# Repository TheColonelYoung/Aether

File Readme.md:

# AETHER
Addressable LED controller powered by WLED. Sound reactive capable with IR receiver. Due to ESP32 is capable to produce FFT effects.
Designed as replacement electronics for SP511e. So it fits the same case.

### Features and components
- Compatible with 12V and 5V strips
- Built-on digital microphone (INMP411) 
    - Works with Sound reactive fork
    - Support FFT effects
- IR receiver for remote control
- Bootloader jumper
- 3 buttons for manual control

### SP511e replacement
This project is designed as replacement for SP511e electronics which is based on ESP8266 which is not capable of FFT effect and can only driver one line of LED strips.
You don't need to have SP511e controller but some part are salvageable. You can 3D print your own case.
Microphone is also replaced with digital omni-directional which has better results.

Some parts are salvageable from original board:
- Cables for LEDs
- IR receiver with cable
- Buttons
- Input power jack
- Case

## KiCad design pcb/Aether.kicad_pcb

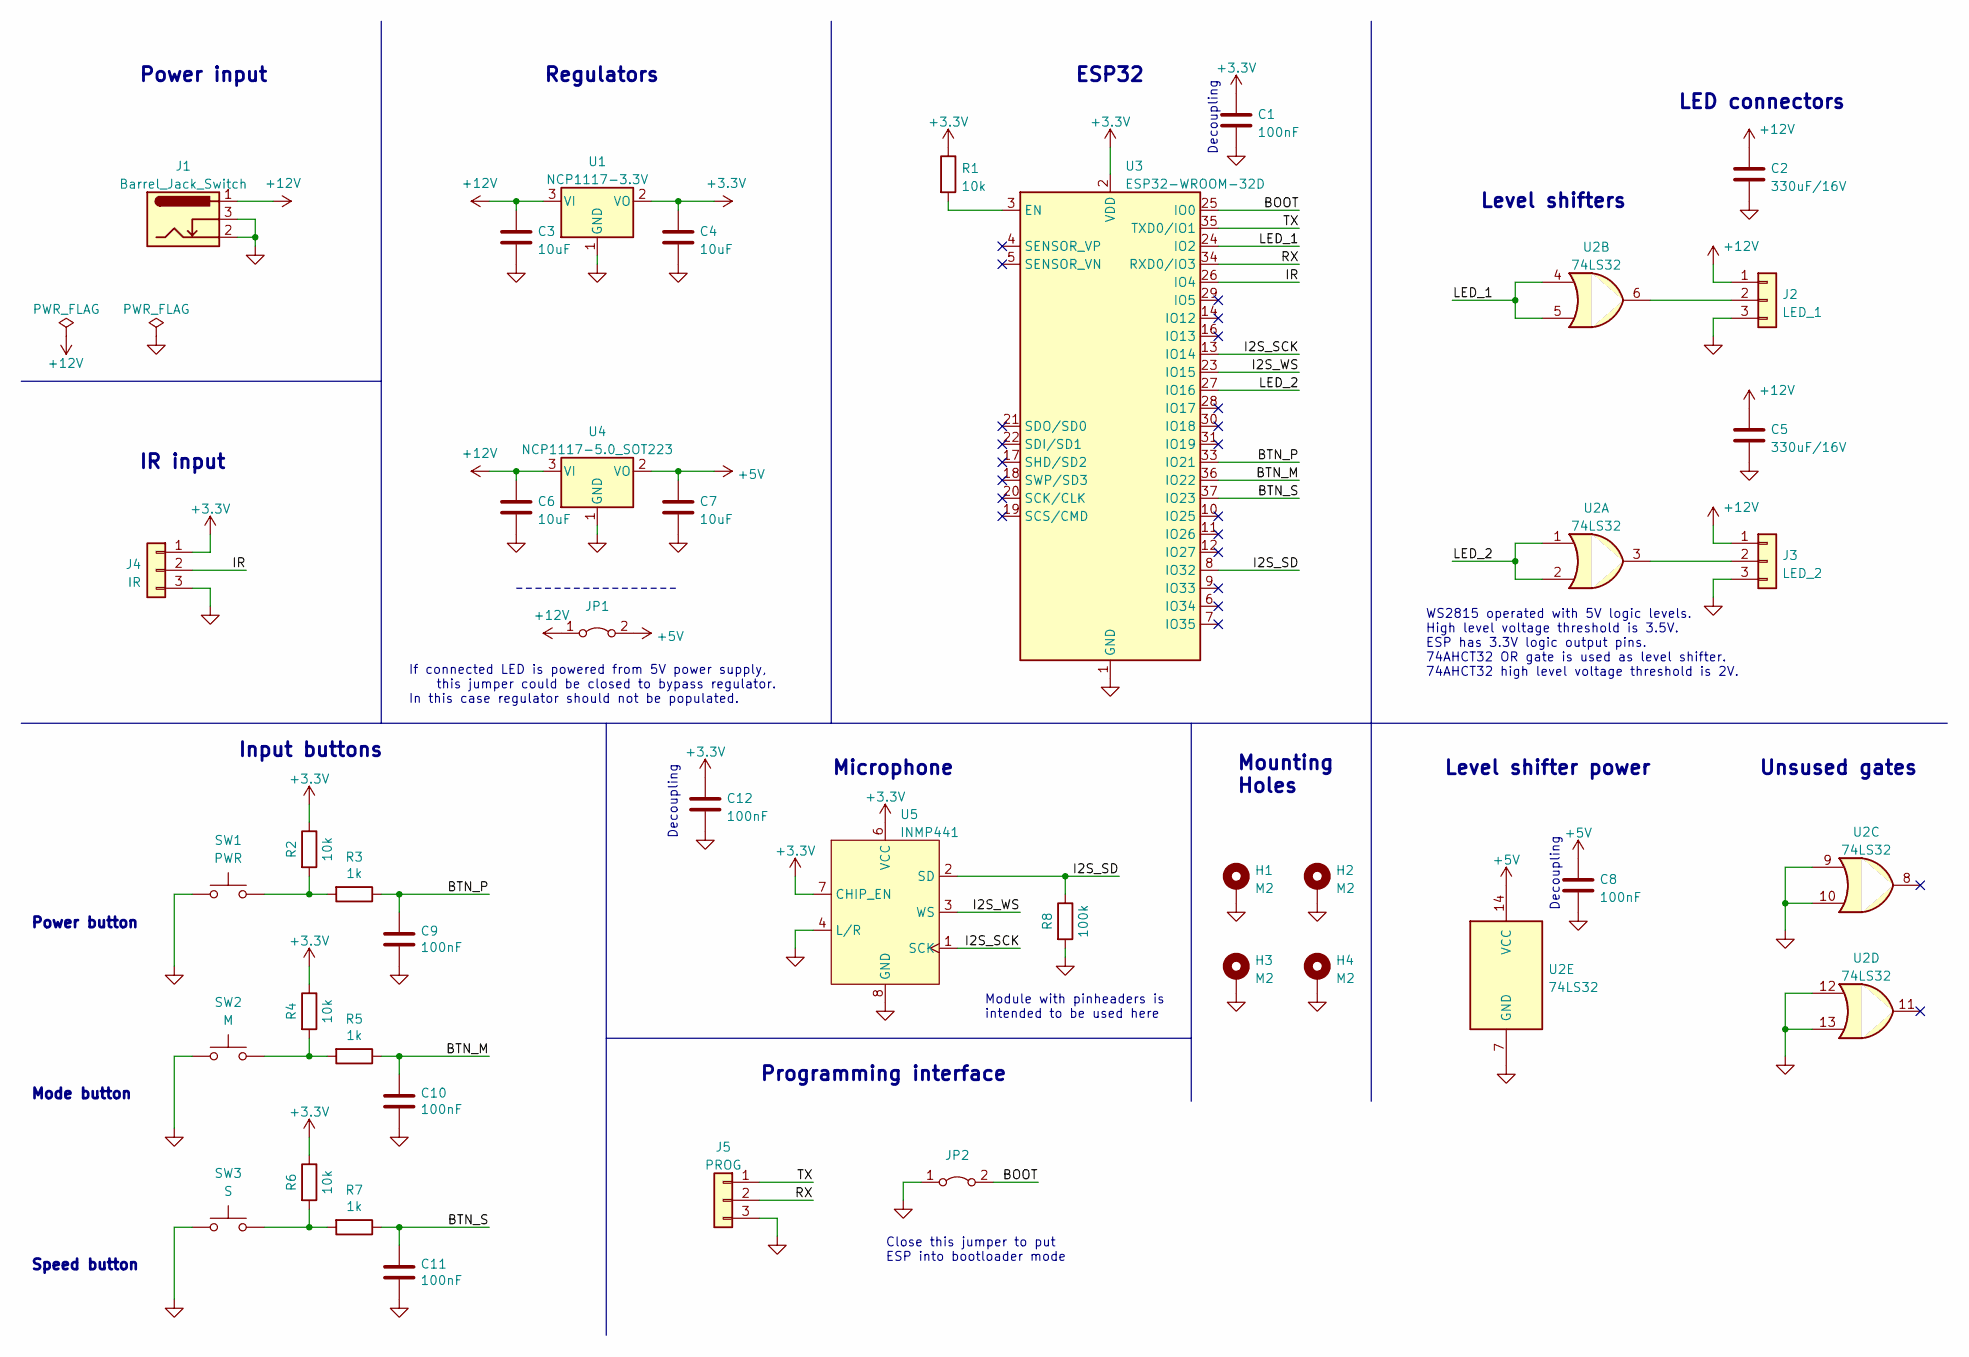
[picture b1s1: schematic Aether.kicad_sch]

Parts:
C1, C8, C9, C10, C11, C12: 100nF; C_0603_1608Metric
C2, C5: 330uF/16V; CP_Elec_6.3x7.7
C3, C4, C6, C7: 10uF; C_0805_2012Metric
H1, H2, H3, H4: M2; MountingHole_2.2mm_M2_Pad_Via
J1: Barrel_Jack_Switch; Barrel_jack_short
J2: LED_1; PinHeader_1x03_P2.54mm_Vertical
J3: LED_2; PinHeader_1x03_P2.54mm_Vertical
J4: IR; PinHeader_1x03_P2.54mm_Vertical
J5: PROG; PinHeader_1x03_P2.54mm_Vertical
JP1: 5V_PASSTHROUGH; SolderJumper-2_P1.3mm_Open_RoundedPad1.0x1.5mm
JP2: BOOT; PinHeader_1x02_P2.54mm_Vertical
R1, R2, R4, R6: 10k; R_0603_1608Metric
R3, R5, R7: 1k; R_0603_1608Metric
R8: 100k; R_0603_1608Metric
SW1: PWR; SW_SPST_TL3342
SW2: M; SW_SPST_TL3342
SW3: S; SW_SPST_TL3342
U1: NCP1117-3.3V; SOT-223-3_TabPin2
U2: 74LS32; Texas_S-PVQFN-N14
U3: ESP32-WROOM-32D; ESP32-WROOM-32
U4: NCP1117-5.0_SOT223; SOT-223-3_TabPin2
U5: INMP441

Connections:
+3.3V: C1.1, C4.1, C12.1, J4.1, R1.1, R2.1, R4.1, R6.1, U1.2 (VO), U3.2 (VDD), U5.6 (VCC), U5.7 (CHIP_EN)
+5V: C7.1, C8.1, JP1.2 (B), U2.14 (VCC), U4.2 (VO)
+12V: C2.1, C3.1, C5.1, C6.1, J1.1, J2.1, J3.1, JP1.1 (A), U1.3 (VI), U4.3 (VI)
/BOOT: JP2.2 (B), U3.25 (IO0)
/BTN_M: C10.1, R5.1, U3.36 (IO22)
/BTN_P: C9.1, R3.1, U3.33 (IO21)
/BTN_S: C11.1, R7.1, U3.37 (IO23)
/I2S_SCK: U3.13 (IO14), U5.1 (SCK)
/I2S_SD: R8.1, U3.8 (IO32), U5.2 (SD)
/I2S_WS: U3.23 (IO15), U5.3 (WS)
/IR: J4.2, U3.26 (IO4)
/LED_1: U2.4, U2.5, U3.24 (IO2)
/LED_2: U2.1, U2.2, U3.27 (IO16)
/RX: J5.2, U3.34 (RXD0/IO3)
/TX: J5.1, U3.35 (TXD0/IO1)
GND: C1.2, C2.2, C3.2, C4.2, C5.2, C6.2, C7.2, C8.2, C9.2, C10.2, C11.2, C12.2, H1.1, H2.1, H3.1, H4.1, J1.2, J1.3, J2.3, J3.3, J4.3, J5.3, JP2.1 (A), R8.2, SW1.1, SW2.1, SW3.1, U1.1 (GND), U2.7 (GND), U2.9, U2.10, U2.12, U2.13, U3.1 (GND), U3.15 (GND), U3.38 (GND), U3.39 (GND), U4.1 (GND), U5.4 (L/R), U5.5 (GND), U5.8 (GND), U5.9 (GND)
unnamed: J2.2, U2.6
unnamed: J3.2, U2.3
unnamed: R1.2, U3.3 (EN)
unnamed: R2.2, R3.2, SW1.2
unnamed: R4.2, R5.2, SW2.2
unnamed: R6.2, R7.2, SW3.2

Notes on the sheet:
Regulators
IR input
WS2815 operated with 5V logic levels. High level voltage threshold is 3.5V. ESP has 3.3V logic output pins. 74AHCT32 OR gate is used as level shifter. 74AHCT32 high level voltage threshold is 2V.
Decoupling
Level shifter power
Input buttons
Power button
Level shifters
Programming interface
LED connectors
ESP32
Mounting Holes
Power input
Close this jumper to put ESP into bootloader mode
Microphone
If connected LED is powered from 5V power supply, this jumper could be closed to bypass regulator. In this case regulator should not be populated.
Module with pinheaders is intended to be used here
Unsused gates
Speed button
Mode button

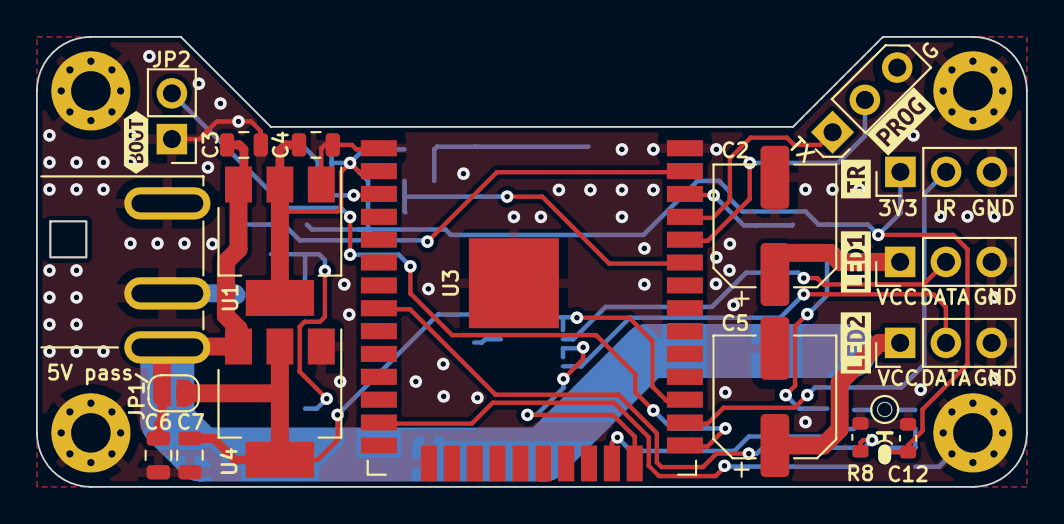
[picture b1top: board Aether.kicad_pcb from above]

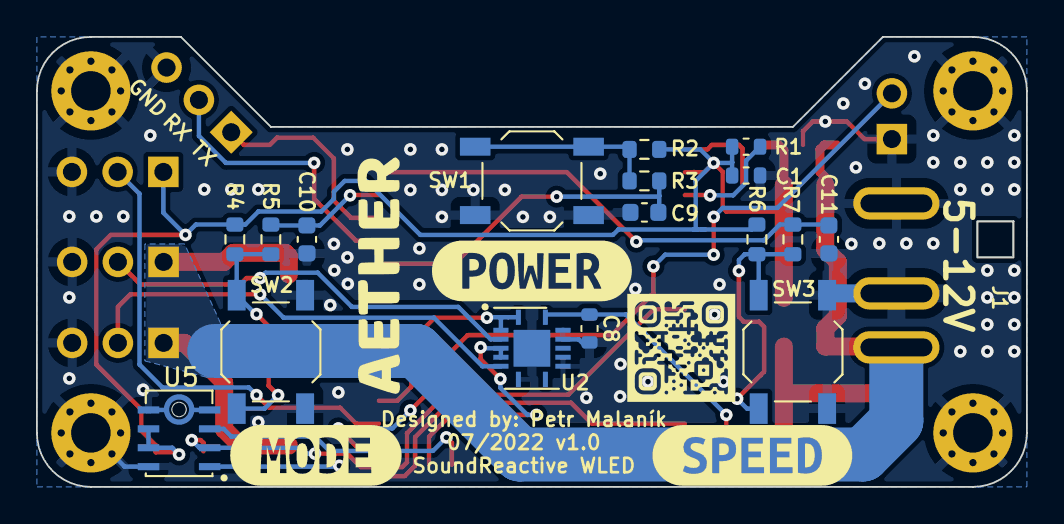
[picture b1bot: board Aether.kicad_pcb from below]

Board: 2 copper layers, 55.0 x 25.0 mm, 47 parts (20 on the bottom side), 22 nets.

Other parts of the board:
kibuzzard-62D1B70F: G***; kibuzzard-62D1B70F
kibuzzard-62D1B640: G***; kibuzzard-62D1B640
kibuzzard-62D1B654: G***; kibuzzard-62D1B654
kibuzzard-62D1B701: G***; kibuzzard-62D1B701
kibuzzard-62D2D12D: G***; kibuzzard-62D2D12D
kibuzzard-62D13E5B: G***; kibuzzard-62D13E5B
kibuzzard-62D13E43: G***; kibuzzard-62D13E43
kibuzzard-62D13E62: G***; kibuzzard-62D13E62

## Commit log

2022-07-11 Schema: Initial parts selection
2022-07-14 Schema: add level shifter, microphone and second LED output
2022-07-16 Schema: add microphone, mounting holes and finalize buttons
2022-07-16 PCB: Done routing of board
2022-07-16 Project: move PCB sources into pcb folder, create Readme
